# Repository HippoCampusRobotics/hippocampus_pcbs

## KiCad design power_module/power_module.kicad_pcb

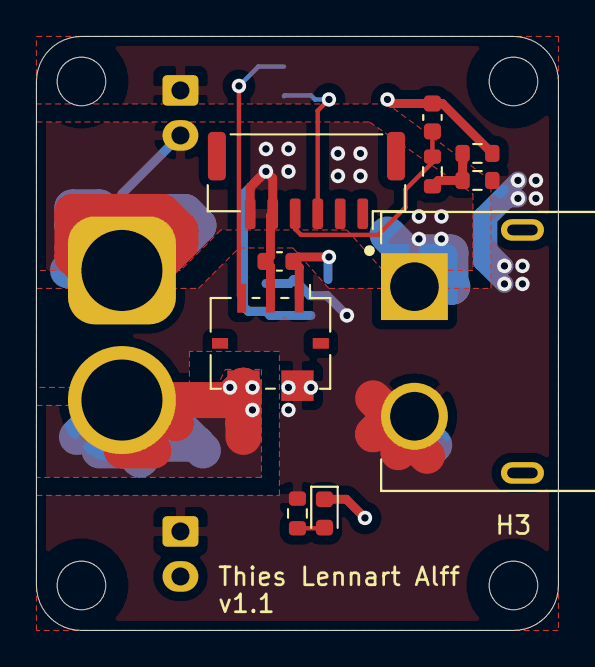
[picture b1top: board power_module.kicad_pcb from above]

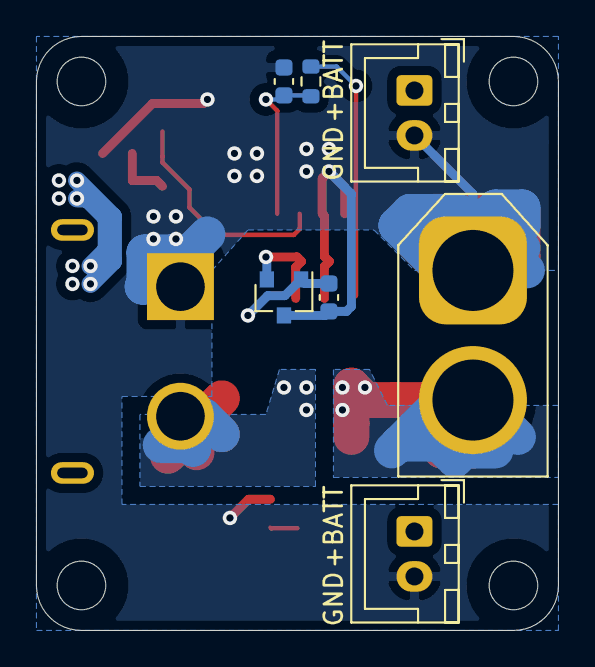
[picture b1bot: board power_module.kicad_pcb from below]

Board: 2 copper layers, 29.0 x 33.0 mm, 21 parts (7 on the bottom side), 9 nets.

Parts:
C1, C2, C3, C4: 100nF; C_0603_1608Metric
D1: SML-D15MWT86; D_0603_1608Metric
H1, H2, H3, H4: MountingHole; MountingHole_2.7mm_M2.5_Masked
J1: XT60PW-M; AMASS_XT60PW-M
J2: XT60U-M; AMASS_XT60-M_1x02_P7.20mm_Vertical
J3, J4: JST-XH; JST_XH_B2B-XH-A_1x02_P2.50mm_Vertical
J5: Conn_01x06; JST_GH_SM06B-GHS-TB_1x06-1MP_P1.25mm_Horizontal
R1, R2, R3: 1k; R_0603_1608Metric
R4: 100k; R_0603_1608Metric
R5: 10k; R_0603_1608Metric
U1: NCV51460; SOT-23
U2: ACS781xLRTR-100U; Allegro_PSOF-7_4.8x6.4mm_P1.60mm

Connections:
+3V3: C2.1, U1.2, U2.1
+BATT: C1.1, J1.2, J3.1, J4.1, R1.2, R4.1, U1.1, U2.6
/+BATT_RAW: J2.2, U2.5
/CURRENT_SENS: C3.1, J5.3, R2.1
/VOLTAGE_SENS: C4.1, J5.4, R3.2
GND: C1.2, C2.2, C3.2, C4.2, D1.1, J1.1, J2.1, J3.2, J4.2, J5.5, J5.6, R5.2, U1.3, U2.2
unnamed: D1.2, R1.1
unnamed: R2.2, U2.3
unnamed: R3.1, R4.2, R5.1

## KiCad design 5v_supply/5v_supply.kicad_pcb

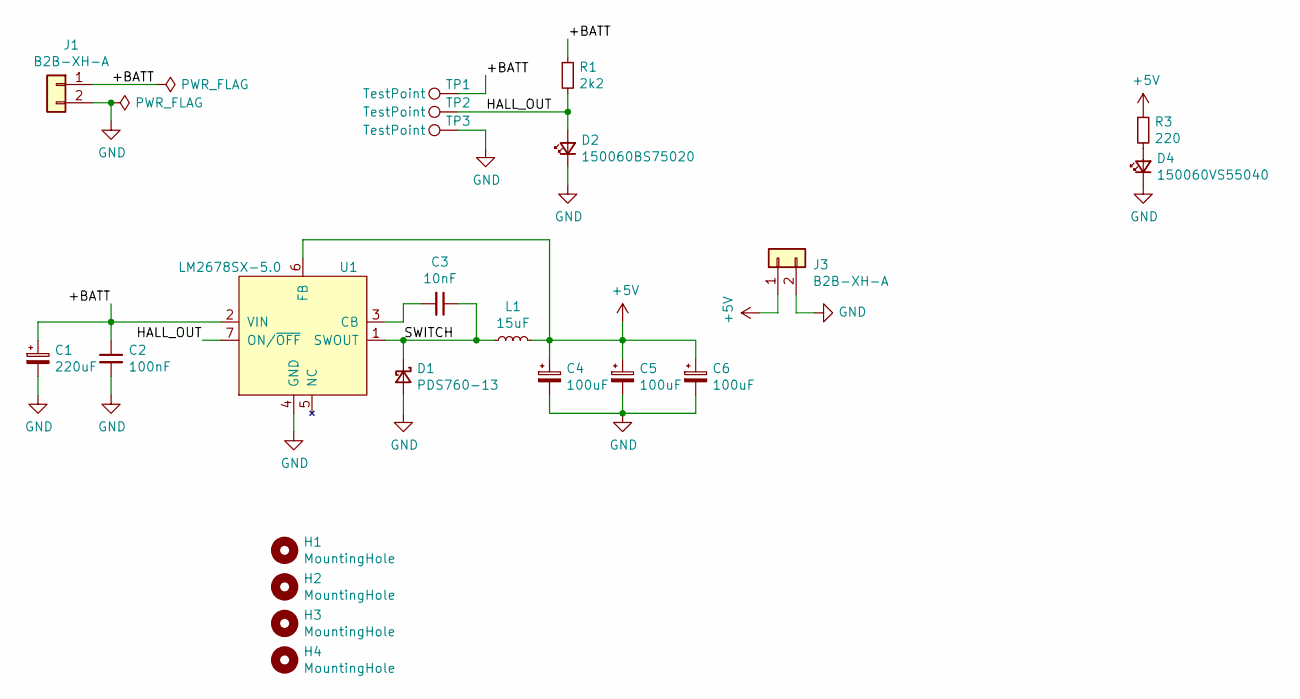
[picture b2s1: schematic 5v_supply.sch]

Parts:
C1: 220uF; CP_Elec_8x11.9; MPN PCH1V221MCL1GS
C2: 100nF; C_0603_1608Metric; MPN CGA3E2X7R1H104K080AA
C3: 10nF; C_0603_1608Metric; MPN C0603C103K3GACTU
C4, C5, C6: 100uF; CP_EIA-3528-21_Kemet-B; MPN 8TPE100MAZB
D1: PDS760-13; D_PowerDI-5; MPN PDS760-13
D2: 150060BS75020; LED_0603_1608Metric; MPN 150060BS75020
D4: 150060VS55040; LED_0603_1608Metric; MPN 150060VS55040
H1, H2, H3, H4: MountingHole; MountingHole_2.7mm_M2.5_Masked
J1, J3: B2B-XH-A; JST_XH_B2B-XH-A_1x02_P2.50mm_Vertical
L1: 15uF; L_LMLP13B3; MPN LMLP13B3M150DTAS
R1: 2k2; R_0603_1608Metric
R3: 220; R_0603_1608Metric
TP1, TP2, TP3: TestPoint; TestPoint_THTPad_D1.5mm_Drill0.7mm
U1: LM2678SX-5.0; TO-263-7_TabPin4

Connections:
+5V: C4.1, C5.1, C6.1, J3.1, L1.2, R3.1, U1.6 (FB)
/+BATT: C1.1, C2.1, J1.1, R1.1, TP1.1, U1.2 (VIN)
/HALL_OUT: D2.2 (A), R1.2, TP2.1, U1.7 (ON/~OFF)
/SWITCH: C3.1, D1.1 (K), L1.1, U1.1 (SWOUT)
GND: C1.2, C2.2, C4.2, C5.2, C6.2, D1.2 (A), D2.1 (K), D4.1 (K), J1.2, J3.2, TP3.1, U1.4 (GND)
unnamed: C3.2, U1.3 (CB)
unnamed: D4.2 (A), R3.2

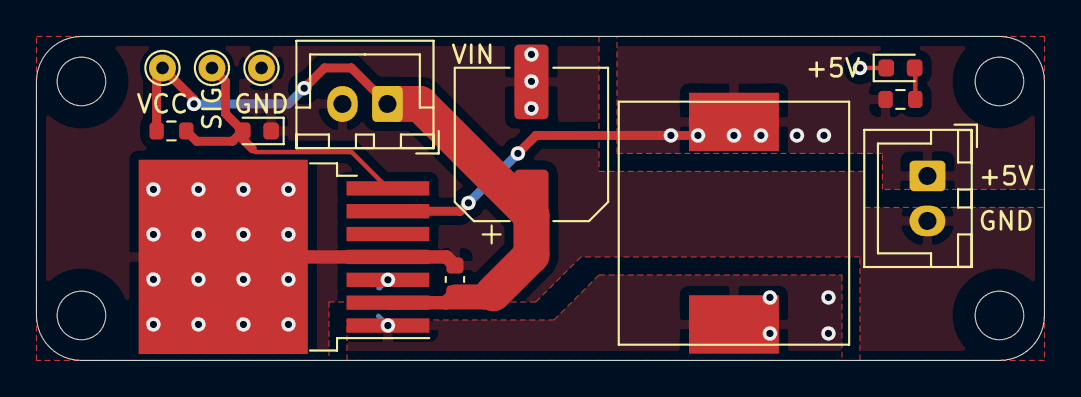
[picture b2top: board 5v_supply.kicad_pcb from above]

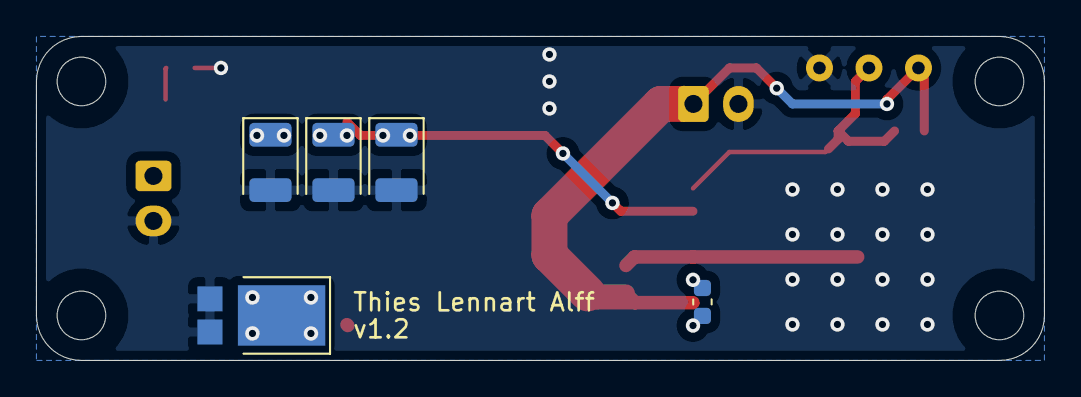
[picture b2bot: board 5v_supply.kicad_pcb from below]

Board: 2 copper layers, 56.0 x 18.0 mm, 22 parts (5 on the bottom side), 7 nets.

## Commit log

2021-02-15 initial version
2021-02-17 first version of buck converter
2021-02-17 changed layout to a more wide format
2021-02-19 moved battery connector to have a safety margin
2021-02-19 removed ignored files
2021-02-19 updated pcb dimensions
2021-02-19 removed ref silksreen print
2021-02-19 updated outdated mounting hole footprint
2021-02-19 replaced hall connector with pads
2021-03-04 added pcb for power connections of the motors
